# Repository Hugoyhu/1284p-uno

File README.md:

# 1284p-uno
UNO form factor 1284P dev board

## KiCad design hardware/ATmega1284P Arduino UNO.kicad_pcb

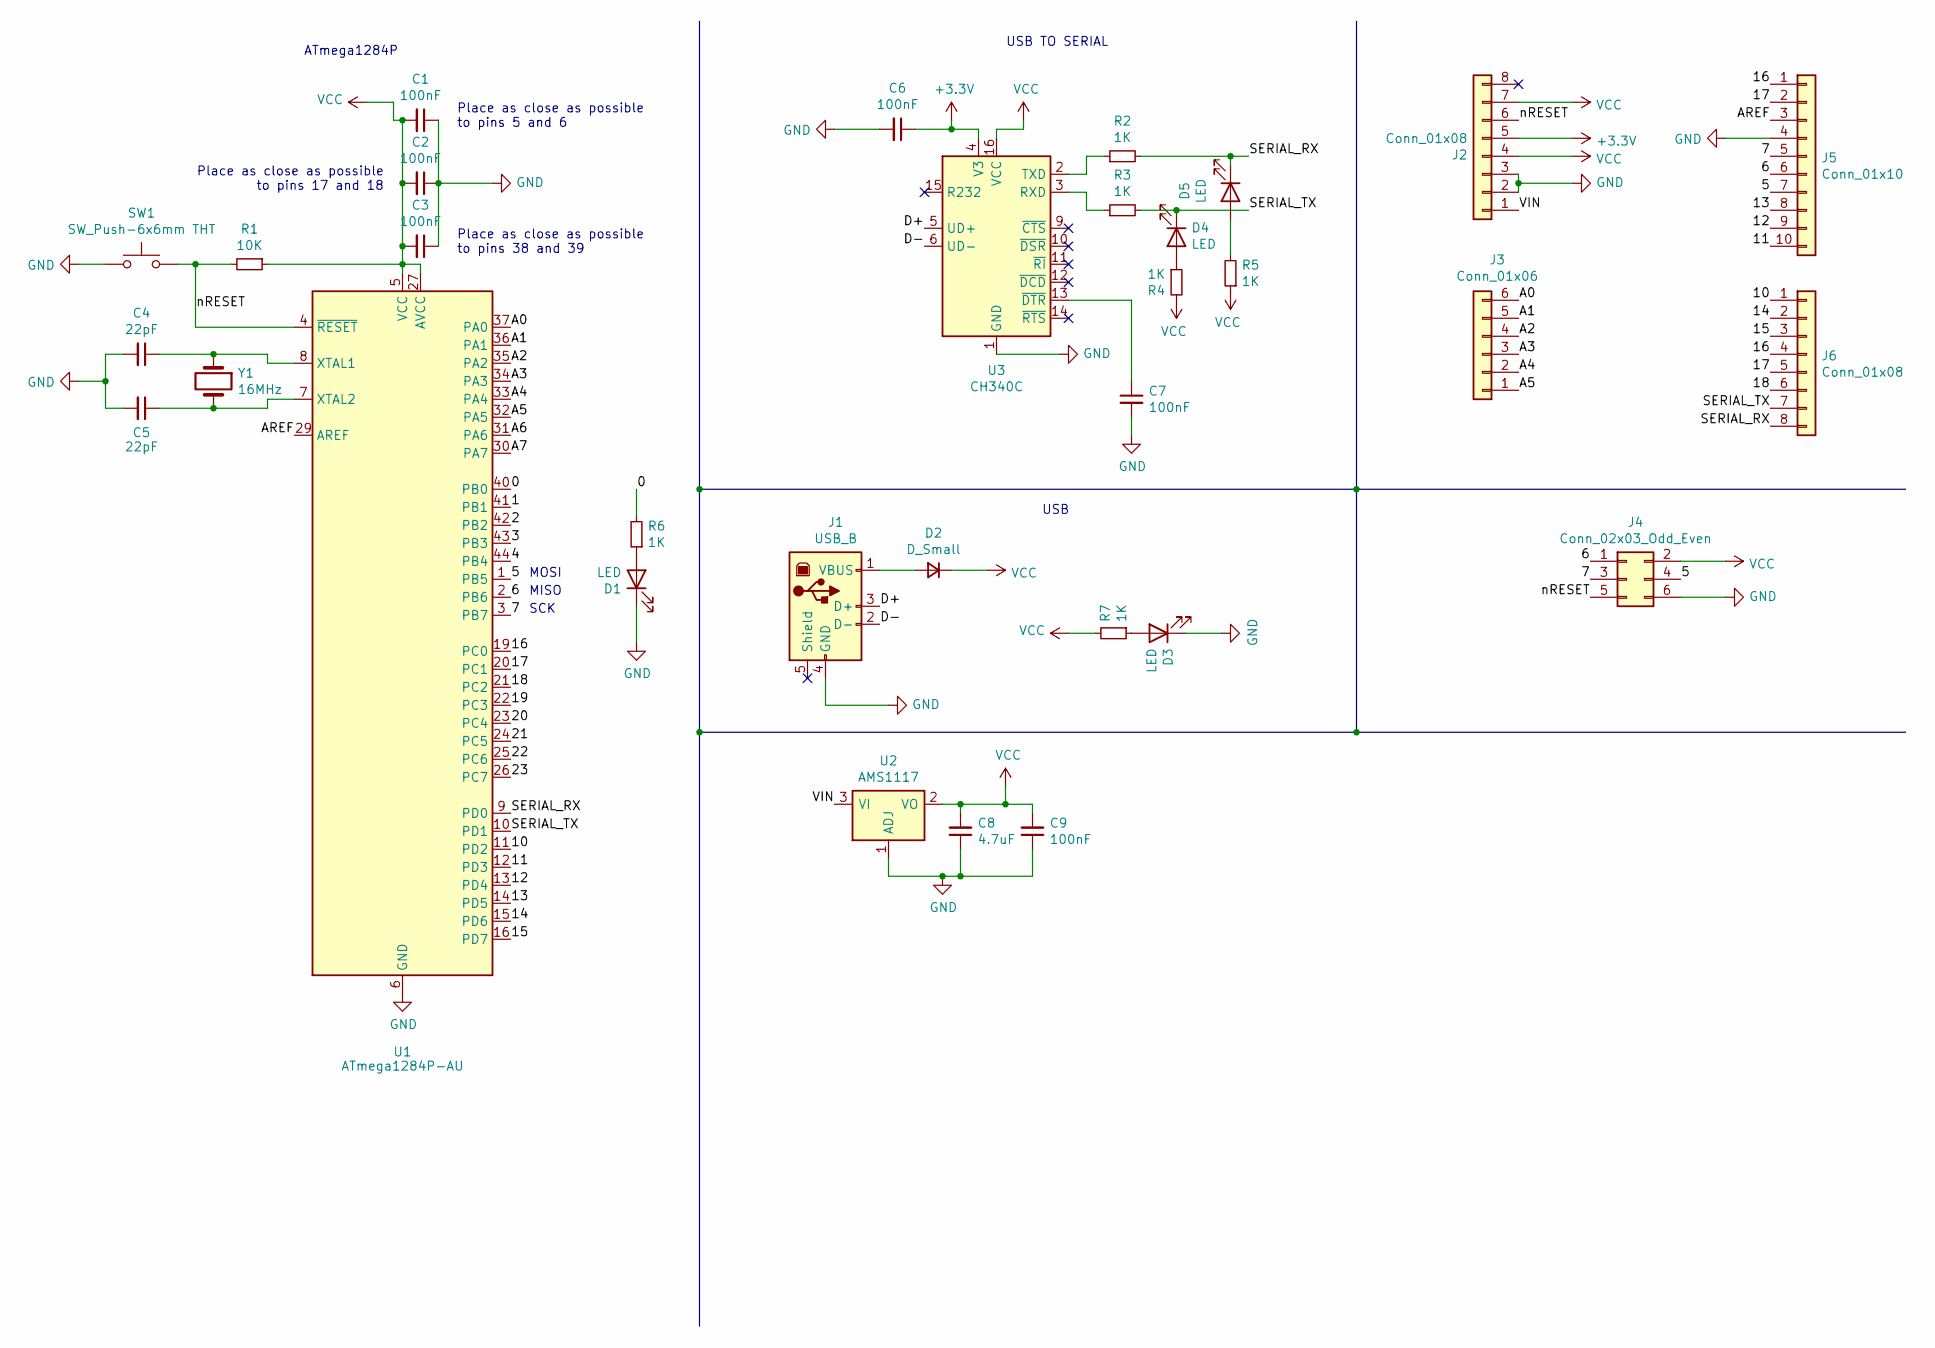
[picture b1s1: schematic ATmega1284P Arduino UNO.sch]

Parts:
C1, C2, C3, C6, C7, C9: 100nF; C_0603_1608Metric_Pad1.08x0.95mm_HandSolder
C4, C5: 22pF; C_0603_1608Metric_Pad1.08x0.95mm_HandSolder
C8: 4.7uF; C_0603_1608Metric_Pad1.08x0.95mm_HandSolder
D1, D3, D4, D5: LED; LED_0603_1608Metric_Pad1.05x0.95mm_HandSolder
D2: D_Small; D_SMF
J1: USB_B; USB_B_Lumberg_2411_02_Horizontal
J2, J6: Conn_01x08; PinSocket_1x08_P2.54mm_Vertical
J3: Conn_01x06; PinSocket_1x06_P2.54mm_Vertical
J4: Conn_02x03_Odd_Even; PinHeader_2x03_P2.54mm_Vertical
J5: Conn_01x10; PinSocket_1x10_P2.54mm_Vertical
R1: 10K; R_0603_1608Metric_Pad0.98x0.95mm_HandSolder
R2, R3, R4, R5, R6, R7: 1K; R_0603_1608Metric_Pad0.98x0.95mm_HandSolder
SW1: SW_Push-6x6mm THT; SW_PUSH_6mm
U1: ATmega1284P-AU; TQFP-44_10x10mm_P0.8mm
U2: AMS1117; SOT-223-3_TabPin2
U3: CH340C; SOIC-16_3.9x9.9mm_P1.27mm
Y1: 16MHz; Crystal_HC49-4H_Vertical

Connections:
+3V3: C6.1, J2.5, U3.4 (V3)
/0: R6.2, U1.40 (PB0)
/1: U1.41 (PB1)
/2: U1.42 (PB2)
/3: U1.43 (PB3)
/4: U1.44 (PB4)
/5: J4.4, J5.7, U1.1 (PB5)
/6: J4.1, J5.6, U1.2 (PB6)
/7: J4.3, J5.5, U1.3 (PB7)
/10: J6.1, U1.11 (PD2)
/11: J5.10, U1.12 (PD3)
/12: J5.9, U1.13 (PD4)
/13: J5.8, U1.14 (PD5)
/14: J6.2, U1.15 (PD6)
/15: J6.3, U1.16 (PD7)
/16: J5.1, J6.4, U1.19 (PC0)
/17: J5.2, J6.5, U1.20 (PC1)
/18: J6.6, U1.21 (PC2)
/19: U1.22 (PC3)
/20: U1.23 (PC4)
/21: U1.24 (PC5)
/22: U1.25 (PC6)
/23: U1.26 (PC7)
/A0: J3.6, U1.37 (PA0)
/A1: J3.5, U1.36 (PA1)
/A2: J3.4, U1.35 (PA2)
/A3: J3.3, U1.34 (PA3)
/A4: J3.2, U1.33 (PA4)
/A5: J3.1, U1.32 (PA5)
/A6: U1.31 (PA6)
/A7: U1.30 (PA7)
/AREF: J5.3, U1.29 (AREF)
/D+: J1.3 (D+), U3.5 (UD+)
/D-: J1.2 (D-), U3.6 (UD-)
/SERIAL_RX: D5.1 (K), J6.8, R2.2, U1.9 (PD0)
/SERIAL_TX: D4.1 (K), J6.7, R3.2, U1.10 (PD1)
/VIN: J2.1, U2.3 (VI)
/nRESET: J2.6, J4.5, R1.2, SW1.2, U1.4 (~RESET)
GND: C1.1, C2.1, C3.1, C4.2, C5.2, C6.2, C7.2, C8.1, C9.1, D1.1 (K), D3.1 (K), J1.4 (GND), J2.2, J2.3, J4.6, J5.4, SW1.1, U1.6 (GND), U1.18 (GND), U1.28 (GND), U1.39 (GND), U2.1 (ADJ), U3.1 (GND)
unnamed: C4.1, U1.8 (XTAL1), Y1.1
unnamed: C5.1, U1.7 (XTAL2), Y1.2
unnamed: C7.1, U3.13 (~DTR)
unnamed: D1.2 (A), R6.1
unnamed: D2.2 (A), J1.1 (VBUS)
unnamed: D3.2 (A), R7.1
unnamed: D4.2 (A), R4.1
unnamed: D5.2 (A), R5.2
unnamed: R2.1, U3.2 (TXD)
unnamed: R3.1, U3.3 (RXD)
VCC: C1.2, C2.2, C3.2, C8.2, C9.2, D2.1 (K), J2.4, J2.7, J4.2, R1.1, R4.2, R5.1, R7.2, U1.5 (VCC), U1.17 (VCC), U1.27 (AVCC), U1.38 (VCC), U2.2 (VO), U3.16 (VCC)

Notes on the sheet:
ATmega1284P
Place as close as possible to pins 5 and 6
Place as close as possible to pins 17 and 18
Place as close as possible to pins 38 and 39
USB TO SERIAL
USB
MOSI
MISO
SCK

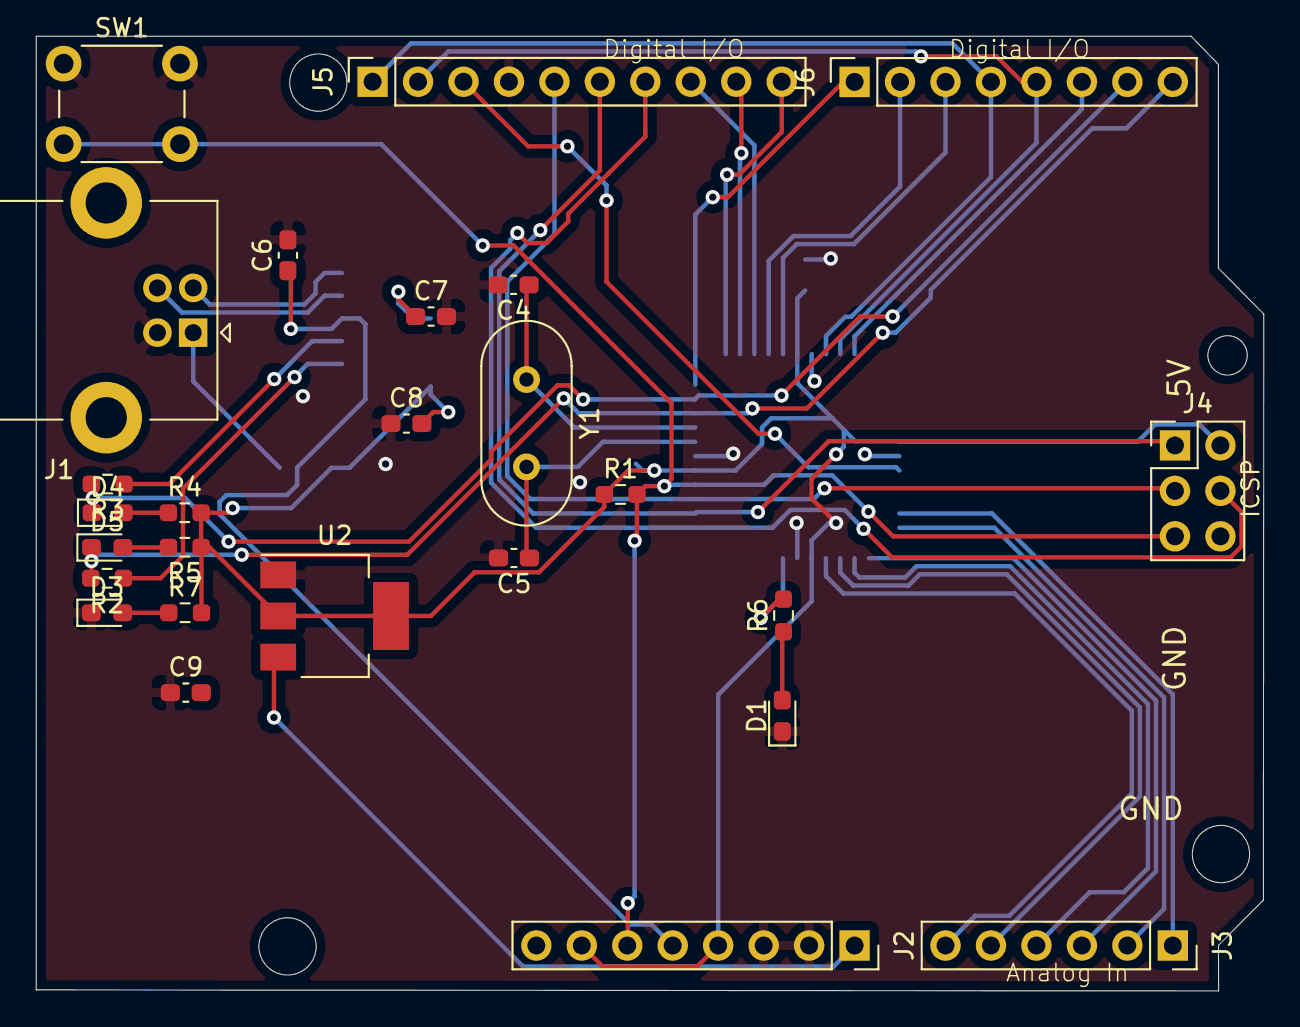
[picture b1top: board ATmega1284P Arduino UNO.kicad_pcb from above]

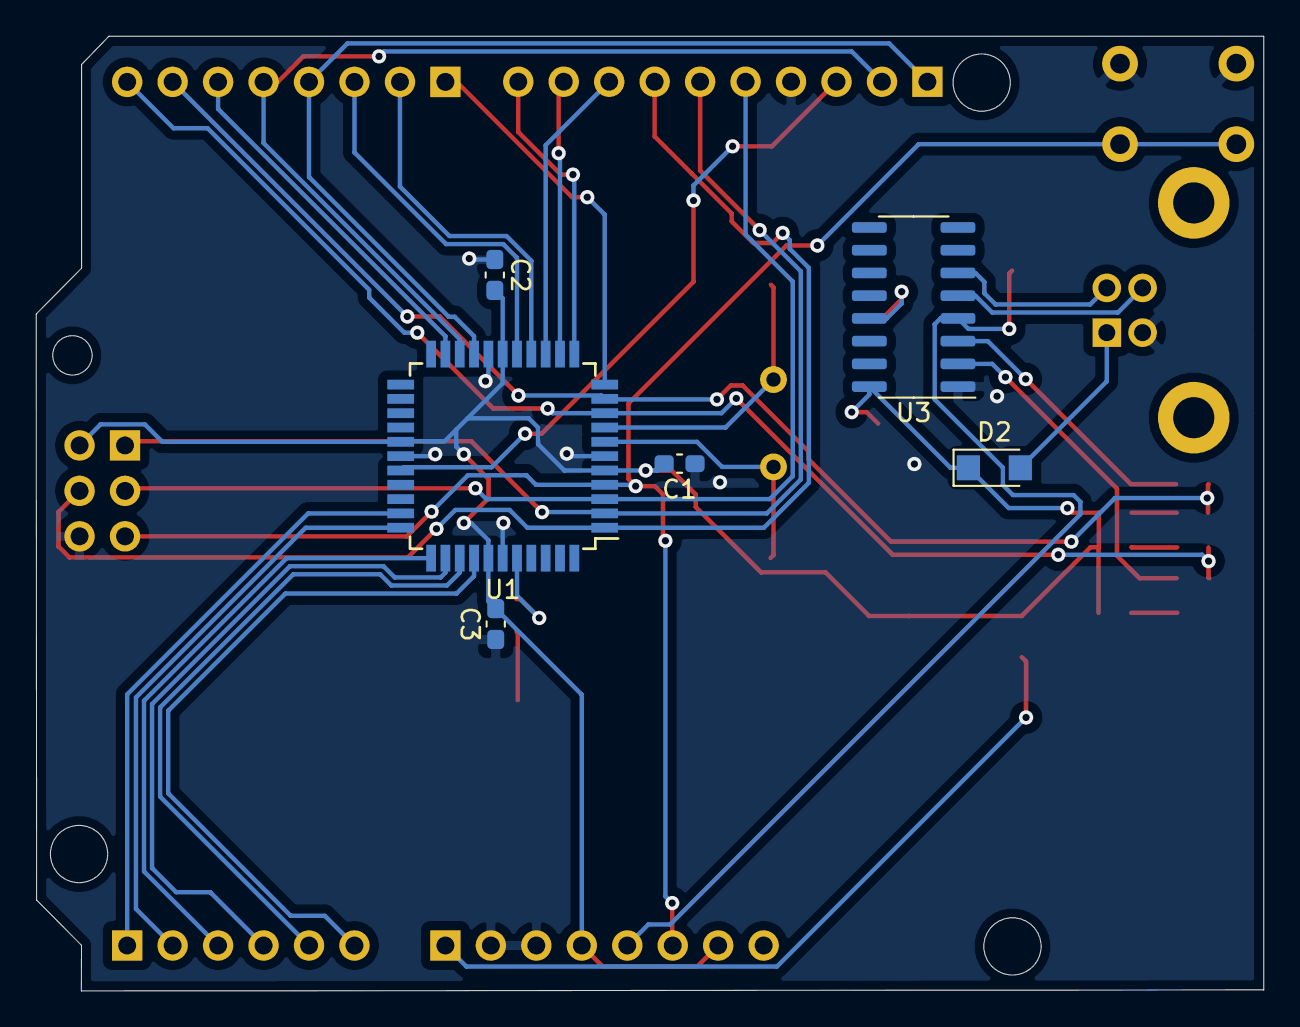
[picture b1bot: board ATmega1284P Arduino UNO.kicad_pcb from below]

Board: 2 copper layers, 68.6 x 53.3 mm, 36 parts (6 on the bottom side), 39 nets.

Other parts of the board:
@HOLE0, @HOLE0#2, @HOLE0#3, @HOLE1: (no value)

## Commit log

2021-02-21 [ImgBot] Optimize images
    *Total -- 237.38kb -> 129.18kb (45.58%)
    /Screen Shot 2021-02-21 at 4.21.23 PM.png -- 123.30kb -> 65.03kb (47.26%)
    /Screen Shot 2021-02-21 at 4.21.13 PM.png -- 114.08kb -> 64.14kb (43.77%)
